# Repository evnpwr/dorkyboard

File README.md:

Dorkyboard
===========
Dorkyboard is a 104-key keyboard with an ISO-style enter key and backslash key, and an otherwise ANSI-like layout. It has a number pad. I know number pads aren't cool, but hey, I'm a dork.
The dorkyboard is in its very early stages. The hardware is completely untested (boards are not yet manufactured) and the firmware is non-existant.
Dorkyboard uses Cherry MX switches. The mechanical design of the Dorkyboard is extrememly minimal. There is no enclosure. The keys are not mounted on a plate. They mount directly to the PCB. The PCB sits on adhesive rubber feet. There are lots and lots of rubber feet to minimize board flex. 
The microcontroller is an Atmel ATMEGA32U4, the same microcontroller used in the Arduino Micro.The microcontroller's supporting circuitry is based on the Arduino Micro.
The Cherry MX PCB footprints are slightly modified versions of the footprints created by Fredrik Atmer of BathroomEpiphanies. The original footprints are available here: https://github.com/BathroomEpiphanies/KiCAD-Keyboard-Tutorial  
Thank you, Mr. Atmer.  
Dorkyboard is an open hardware project. It is licensed under the CERN OHL v1.2. It is designed using KiCad.

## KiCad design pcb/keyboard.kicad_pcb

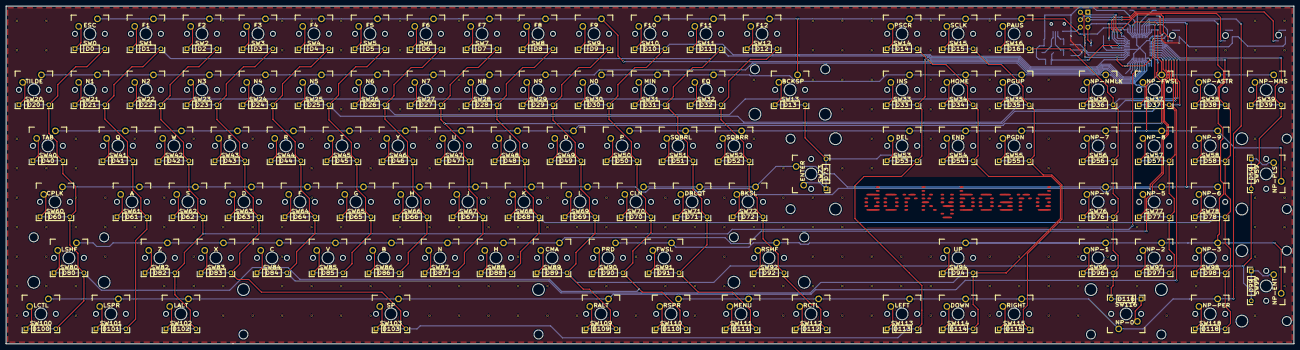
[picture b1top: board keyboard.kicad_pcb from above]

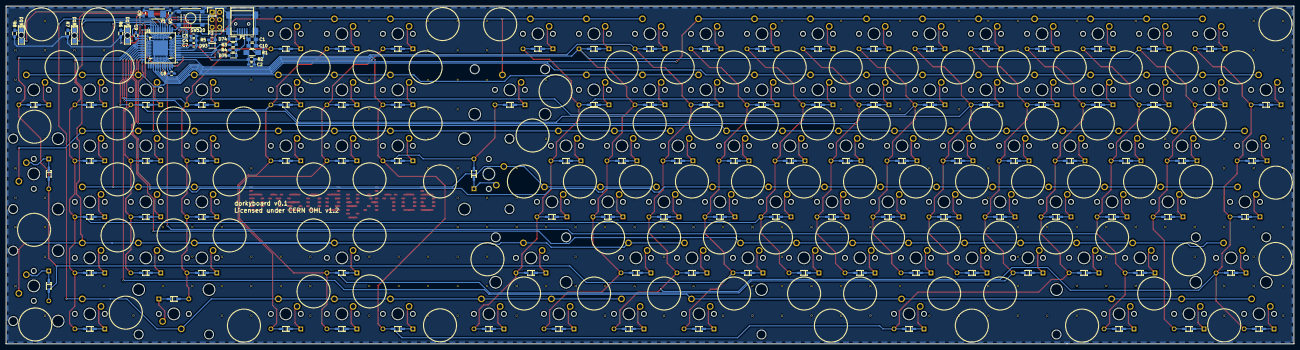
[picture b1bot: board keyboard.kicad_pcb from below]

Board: 2 copper layers, 436.8 x 114.6 mm, 237 parts (29 on the bottom side), 146 nets.

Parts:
C1, C10: 10uF; C_0805_HandSoldering
C2, C3, C4, C8: 100nF; C_0603_HandSoldering
C5, C6: 22pF; C_0603_HandSoldering
C7, C9: 1uF; C_0603_HandSoldering
D0, D1, D2, D3, D4, D5, D6, D7, D8, D9, D10, D11, D12, D13, D14, D15, D16, D20, D21, D22, D23, D24, D25, D26, D27, D28, D29, D30, D31, D32, D33, D34, D35, D36, D37, D38, D39, D40, D41, D42, D43, D44, D45, D46, D47, D48, D49, D50, D51, D52, D53, D54, D55, D56, D57, D58, D59, D60, D61, D62, D63, D64, D65, D66, D67, D68, D69, D70, D71, D72, D73, D76, D77, D78, D80, D82, D83, D84, D85, D86, D87, D88, D89, D90, D91, D92, D94, D96, D97, D98, D99, D100, D101, D102, D103, D109, D110, D111, D112, D113, D114, D115, D116, D118: D_Small; DIODE_TH-SMT
D17, D18, D19: Led_Small; LED Reverse Mount 3.2x1.6mm Dialight
D74, D75: 6.2V; SOD-323_HandSoldering
D93: 1N4148; SOD-323
P1: USB_MiniB; USB_Mini-B
P2: Do Not Populate; Pin_Header_Straight_2x03
R1: 10R Fusible; R_1206_HandSoldering
R2, R5: 10k; R_0603_HandSoldering
R3, R4: 22R; R_0603_HandSoldering
R6, R7, R8: 604R; R_0603_HandSoldering
SW0: ESC; CHERRY_PCB_100H
SW1: F1; CHERRY_PCB_100H
SW2: F2; CHERRY_PCB_100H
SW3: F3; CHERRY_PCB_100H
SW4: F4; CHERRY_PCB_100H
SW5: F5; CHERRY_PCB_100H
SW6: F6; CHERRY_PCB_100H
SW7: F7; CHERRY_PCB_100H
SW8: F8; CHERRY_PCB_100H
SW9: F9; CHERRY_PCB_100H
SW10: F10; CHERRY_PCB_100H
SW11: F11; CHERRY_PCB_100H
SW12: F12; CHERRY_PCB_100H
SW13: BCKSP; CHERRY_PCB_200H
SW14: PSCR; CHERRY_PCB_100H
SW15: SCLK; CHERRY_PCB_100H
SW16: PAUS; CHERRY_PCB_100H
SW20: TILDE; CHERRY_PCB_100H
SW21: N1; CHERRY_PCB_100H
SW22: N2; CHERRY_PCB_100H
SW23: N3; CHERRY_PCB_100H
SW24: N4; CHERRY_PCB_100H
SW25: N5; CHERRY_PCB_100H
SW26: N6; CHERRY_PCB_100H
SW27: N7; CHERRY_PCB_100H
SW28: N8; CHERRY_PCB_100H
SW29: N9; CHERRY_PCB_100H
SW30: N0; CHERRY_PCB_100H
SW31: MIN; CHERRY_PCB_100H
SW32: EQ; CHERRY_PCB_100H
SW33: INS; CHERRY_PCB_100H
SW34: HOME; CHERRY_PCB_100H
SW35: PGUP; CHERRY_PCB_100H
SW36: NP-NMLK; CHERRY_PCB_100H
SW37: NP-FWSL; CHERRY_PCB_100H
SW38: NP-ASTR; CHERRY_PCB_100H
SW39: NP-MNS; CHERRY_PCB_100H
SW40: TAB; CHERRY_PCB_150H
SW41: Q; CHERRY_PCB_100H
SW42: W; CHERRY_PCB_100H
SW43: E; CHERRY_PCB_100H
SW44: R; CHERRY_PCB_100H
SW45: T; CHERRY_PCB_100H
SW46: Y; CHERRY_PCB_100H
SW47: U; CHERRY_PCB_100H
SW48: I; CHERRY_PCB_100H
SW49: O; CHERRY_PCB_100H
SW50: P; CHERRY_PCB_100H
SW51: SQBRL; CHERRY_PCB_100H
SW52: SQBRR; CHERRY_PCB_100H
SW53: DEL; CHERRY_PCB_100H
SW54: END; CHERRY_PCB_100H
SW55: PGDN; CHERRY_PCB_100H
SW56: NP-7; CHERRY_PCB_100H
SW57: NP-8; CHERRY_PCB_100H
SW58: NP-9; CHERRY_PCB_100H
SW59: NP-PLS; CHERRY_PCB_200V
SW60: CPLK; CHERRY_PCB_175H
SW61: A; CHERRY_PCB_100H
SW62: S; CHERRY_PCB_100H
SW63: D; CHERRY_PCB_100H
SW64: F; CHERRY_PCB_100H
SW65: G; CHERRY_PCB_100H
SW66: H; CHERRY_PCB_100H
SW67: J; CHERRY_PCB_100H
SW68: K; CHERRY_PCB_100H
SW69: L; CHERRY_PCB_100H
SW70: CLN; CHERRY_PCB_100H
SW71: DBLQT; CHERRY_PCB_100H
SW72: BKSL; CHERRY_PCB_100H
SW73: ENTER; CHERRY_PCB_ISOR
SW76: NP-4; CHERRY_PCB_100H
SW77: NP-5; CHERRY_PCB_100H
SW78: NP-6; CHERRY_PCB_100H
SW80: LSHF; CHERRY_PCB_225H
SW82: Z; CHERRY_PCB_100H
SW83: X; CHERRY_PCB_100H
SW84: C; CHERRY_PCB_100H
SW85: V; CHERRY_PCB_100H
SW86: B; CHERRY_PCB_100H
SW87: N; CHERRY_PCB_100H
SW88: M; CHERRY_PCB_100H
SW89: CMA; CHERRY_PCB_100H
SW90: PRD; CHERRY_PCB_100H
SW91: FWSL; CHERRY_PCB_100H
SW92: RSHF; CHERRY_PCB_275H
SW94: UP; CHERRY_PCB_100H
SW96: NP-1; CHERRY_PCB_100H
SW97: NP-2; CHERRY_PCB_100H
SW98: NP-3; CHERRY_PCB_100H
SW99: NP-ENT; CHERRY_PCB_200V
SW100: LCTL; CHERRY_PCB_125H
SW101: LSPR; CHERRY_PCB_125H
SW102: LALT; CHERRY_PCB_125H
SW103: SP; CHERRY_PCB_625H
SW109: RALT; CHERRY_PCB_125H
SW110: RSPR; CHERRY_PCB_125H
SW111: MENU; CHERRY_PCB_125H
SW112: RCTL; CHERRY_PCB_125H
SW113: LEFT; CHERRY_PCB_100H
SW114: DOWN; CHERRY_PCB_100H
SW115: RIGHT; CHERRY_PCB_100H
SW116: NP-0; CHERRY_PCB_200H
SW118: NP-PER; CHERRY_PCB_100H
SW120: SW_P; SW_SPST_PTS645
U1: ATMEGA32U4-M; QFN44-7x7mm-QFP-10x10mm
Y1: 16MHz; Crystal_SMD_5032_2Pads

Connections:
+5V: C9.1, D93.1, P2.2, R5.1, U1.2, U1.14, U1.24, U1.34, U1.44
/matrix/Col0: D0.1, D10.1, D20.1, D30.1, D40.1, D50.1, D60.1, D70.1, D80.1, D90.1, D100.1, D110.1, U1.1
/matrix/Col1: D1.1, D11.1, D21.1, D31.1, D41.1, D51.1, D61.1, D71.1, D91.1, D101.1, D111.1, U1.41
/matrix/Col2: D2.1, D12.1, D22.1, D32.1, D42.1, D52.1, D62.1, D72.1, D82.1, D92.1, D102.1, D112.1, U1.40
/matrix/Col3: D3.1, D13.1, D23.1, D33.1, D43.1, D53.1, D63.1, D73.1, D83.1, D103.1, D113.1, U1.39
/matrix/Col4: D4.1, D14.1, D24.1, D34.1, D44.1, D54.1, D64.1, D84.1, D94.1, D114.1, U1.38
/matrix/Col5: D5.1, D15.1, D25.1, D35.1, D45.1, D55.1, D65.1, D85.1, D115.1, U1.29
/matrix/Col6: D6.1, D16.1, D26.1, D36.1, D46.1, D56.1, D66.1, D76.1, D86.1, D96.1, D116.1, U1.28
/matrix/Col7: D7.1, D27.1, D37.1, D47.1, D57.1, D67.1, D77.1, D87.1, D97.1, U1.27
/matrix/Col8: D8.1, D28.1, D38.1, D48.1, D58.1, D68.1, D78.1, D88.1, D98.1, D118.1, U1.26
/matrix/Col9: D9.1, D29.1, D39.1, D49.1, D59.1, D69.1, D89.1, D99.1, D109.1, U1.25
/matrix/LED0: D17.2, U1.8
/matrix/LED1: D18.2, P2.3, U1.9
/matrix/LED2: D19.2, P2.4, U1.10
/matrix/Row0: SW100.1, SW101.1, SW102.1, SW103.1, SW109.1, U1.30
/matrix/Row1: SW110.1, SW111.1, SW112.1, SW113.1, SW114.1, SW115.1, SW116.1, SW118.1, U1.18
/matrix/Row2: SW80.1, SW82.1, SW83.1, SW84.1, SW85.1, SW86.1, SW87.1, SW88.1, SW89.1, U1.31
/matrix/Row3: SW90.1, SW91.1, SW92.1, SW94.1, SW96.1, SW97.1, SW98.1, SW99.1, U1.19
/matrix/Row4: SW60.1, SW61.1, SW62.1, SW63.1, SW64.1, SW65.1, SW66.1, SW67.1, SW68.1, SW69.1, U1.32
/matrix/Row5: SW70.1, SW71.1, SW72.1, SW73.1, SW76.1, SW77.1, SW78.1, U1.20
/matrix/Row6: SW40.1, SW41.1, SW42.1, SW43.1, SW44.1, SW45.1, SW46.1, SW47.1, SW48.1, SW49.1, U1.33
/matrix/Row7: SW50.1, SW51.1, SW52.1, SW53.1, SW54.1, SW55.1, SW56.1, SW57.1, SW58.1, SW59.1, U1.21
/matrix/Row8: SW20.1, SW21.1, SW22.1, SW23.1, SW24.1, SW25.1, SW26.1, SW27.1, SW28.1, SW29.1, U1.36
/matrix/Row9: SW30.1, SW31.1, SW32.1, SW33.1, SW34.1, SW35.1, SW36.1, SW37.1, SW38.1, SW39.1, U1.22
/matrix/Row10: SW0.1, SW1.1, SW2.1, SW3.1, SW4.1, SW5.1, SW6.1, SW7.1, SW8.1, SW9.1, U1.37
/matrix/Row11: SW10.1, SW11.1, SW12.1, SW13.1, SW14.1, SW15.1, SW16.1, U1.12
/microcontroller/MISO: P2.1, U1.11
/microcontroller/RESET: C3.1, C4.1, D93.2, P2.5, R5.2, SW120.2, U1.13
/microcontroller/VUSB: C2.1, R1.2, R2.1, U1.7
GND: C1.2, C2.2, C3.2, C4.2, C5.2, C6.2, C7.2, C8.2, C9.2, C10.2, D74.2, D75.2, P1.5, P1.6, P2.6, R2.2, R6.2, R7.2, R8.2, SW120.1, U1.5, U1.15, U1.23, U1.35, U1.43
unnamed: C1.1, C10.1, P1.1, R1.1
unnamed: C5.1, U1.17, Y1.1
unnamed: C6.1, U1.16, Y1.2
unnamed: C7.1, U1.6
unnamed: C8.1, U1.42
unnamed: D0.2, SW0.2
unnamed: D1.2, SW1.2
unnamed: D2.2, SW2.2
unnamed: D3.2, SW3.2
unnamed: D4.2, SW4.2
unnamed: D5.2, SW5.2
unnamed: D6.2, SW6.2
unnamed: D7.2, SW7.2
unnamed: D8.2, SW8.2
unnamed: D9.2, SW9.2
unnamed: D10.2, SW10.2
unnamed: D11.2, SW11.2
unnamed: D12.2, SW12.2
unnamed: D13.2, SW13.2
unnamed: D14.2, SW14.2
unnamed: D15.2, SW15.2
unnamed: D16.2, SW16.2
unnamed: D17.1, R6.1
unnamed: D18.1, R7.1
unnamed: D19.1, R8.1
unnamed: D20.2, SW20.2
unnamed: D21.2, SW21.2
unnamed: D22.2, SW22.2
unnamed: D23.2, SW23.2
unnamed: D24.2, SW24.2
unnamed: D25.2, SW25.2
unnamed: D26.2, SW26.2
unnamed: D27.2, SW27.2
unnamed: D28.2, SW28.2
unnamed: D29.2, SW29.2
unnamed: D30.2, SW30.2
unnamed: D31.2, SW31.2
unnamed: D32.2, SW32.2
unnamed: D33.2, SW33.2
unnamed: D34.2, SW34.2
unnamed: D35.2, SW35.2
unnamed: D36.2, SW36.2
unnamed: D37.2, SW37.2
unnamed: D38.2, SW38.2
unnamed: D39.2, SW39.2
unnamed: D40.2, SW40.2
unnamed: D41.2, SW41.2
unnamed: D42.2, SW42.2
unnamed: D43.2, SW43.2
unnamed: D44.2, SW44.2
unnamed: D45.2, SW45.2
unnamed: D46.2, SW46.2
unnamed: D47.2, SW47.2
unnamed: D48.2, SW48.2
unnamed: D49.2, SW49.2
unnamed: D50.2, SW50.2
unnamed: D51.2, SW51.2
unnamed: D52.2, SW52.2
unnamed: D53.2, SW53.2
unnamed: D54.2, SW54.2
unnamed: D55.2, SW55.2
unnamed: D56.2, SW56.2
unnamed: D57.2, SW57.2
unnamed: D58.2, SW58.2
unnamed: D59.2, SW59.2
unnamed: D60.2, SW60.2
unnamed: D61.2, SW61.2
unnamed: D62.2, SW62.2
unnamed: D63.2, SW63.2
unnamed: D64.2, SW64.2
unnamed: D65.2, SW65.2
unnamed: D66.2, SW66.2
unnamed: D67.2, SW67.2
unnamed: D68.2, SW68.2
unnamed: D69.2, SW69.2
unnamed: D70.2, SW70.2
unnamed: D71.2, SW71.2
unnamed: D72.2, SW72.2
unnamed: D73.2, SW73.2
unnamed: D74.1, P1.3, R3.1
unnamed: D75.1, P1.2, R4.1
unnamed: D76.2, SW76.2
unnamed: D77.2, SW77.2
unnamed: D78.2, SW78.2
unnamed: D80.2, SW80.2
unnamed: D82.2, SW82.2
unnamed: D83.2, SW83.2
unnamed: D84.2, SW84.2
unnamed: D85.2, SW85.2
unnamed: D86.2, SW86.2
unnamed: D87.2, SW87.2
unnamed: D88.2, SW88.2
unnamed: D89.2, SW89.2
unnamed: D90.2, SW90.2
unnamed: D91.2, SW91.2
unnamed: D92.2, SW92.2
unnamed: D94.2, SW94.2
unnamed: D96.2, SW96.2
unnamed: D97.2, SW97.2
unnamed: D98.2, SW98.2
unnamed: D99.2, SW99.2
unnamed: D100.2, SW100.2
unnamed: D101.2, SW101.2
unnamed: D102.2, SW102.2
unnamed: D103.2, SW103.2
unnamed: D109.2, SW109.2
unnamed: D110.2, SW110.2
unnamed: D111.2, SW111.2
unnamed: D112.2, SW112.2
unnamed: D113.2, SW113.2
unnamed: D114.2, SW114.2
unnamed: D115.2, SW115.2
unnamed: D116.2, SW116.2
unnamed: D118.2, SW118.2
unnamed: R3.2, U1.4
unnamed: R4.2, U1.3

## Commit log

2016-12-12 Add README.md
2016-12-12 Fixed formatting
2016-12-12 new file: pcb/keyboard.kicad_pcb new file: pcb/keyboard.pro new file: pcb/keyboard.sch new file: pcb/matrix.sch new file: pcb/microcontroller.sch new file: pcb/placeDiodes.py
2016-12-12 new file: pcb/LedReverseMount3_2x1_6mmDialight.pretty/LED Reverse Mount 3.2x1.6mm Dialight.kicad_mod new file: pcb/QFN44-7x7mm-QFP-10x10mm.pretty/QFN44-7x7mm-QFP-10x10mm.kicad_mod new file: pcb/pcbLo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
2016-12-15 modified: ../README.md modified: LedReverseMount3_2x1_6mmDialight.pretty/LED Reverse Mount 3.2x1.6mm Dialight.kicad_mod new file: cern_ohl_v_1_2.txt new file: cern_ohl_v_1_2_howto.pdf new file: chang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

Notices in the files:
pcb/keyboard.kicad_pcb:
Licensed under CERN OHL v1.2
